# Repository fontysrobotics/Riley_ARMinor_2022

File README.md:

# Riley_ARMinor_2022
Remote indoor Inspection with Low-cost robots (RILey)
## Github file structure
- `docs` : in-development website containing documentation for the RILey robot, as well as pictures of the robot and meta information. Ideally could be run through Github Pages (can be setup in repository settings) but can also be built and run locally through VSCode.
- `documentation` : All documentation created during the project. This includes the initial project information, the plan of approach (before project requirements shifted drastically), datasheets for some of the components, the technical documentation for setting up many aspects of the robot and server systems, plus additional video material.
- `electrical` : Documentation related to the electrical design of the RILey robot, including version 1 and 2 of the PCB design, notes regarding problems encountered in the PCB design and explanations/schematics for the global electrical connections.
- `ros2` : Code files needed to run the robot (physical and simulation) through ROS2-foxy. More info included in technical document. Included are:
  - `riley_ws` : Main ROS workspace containing all the packages and launch files for both robot and server side.
  - `simulation` : ROS workspace used for simulating the robot in a virtual environment (Gazebo).
  - `yolov5` : Separate directory used to store the YOLOv5 object recognition model.
- `solidworks` : Solidworks CAD files making up version 1 and 2 of the RILey robot, including imported assets. Additional folders for STL/DXF component exports also available, though not needed for the CAD assemblies.

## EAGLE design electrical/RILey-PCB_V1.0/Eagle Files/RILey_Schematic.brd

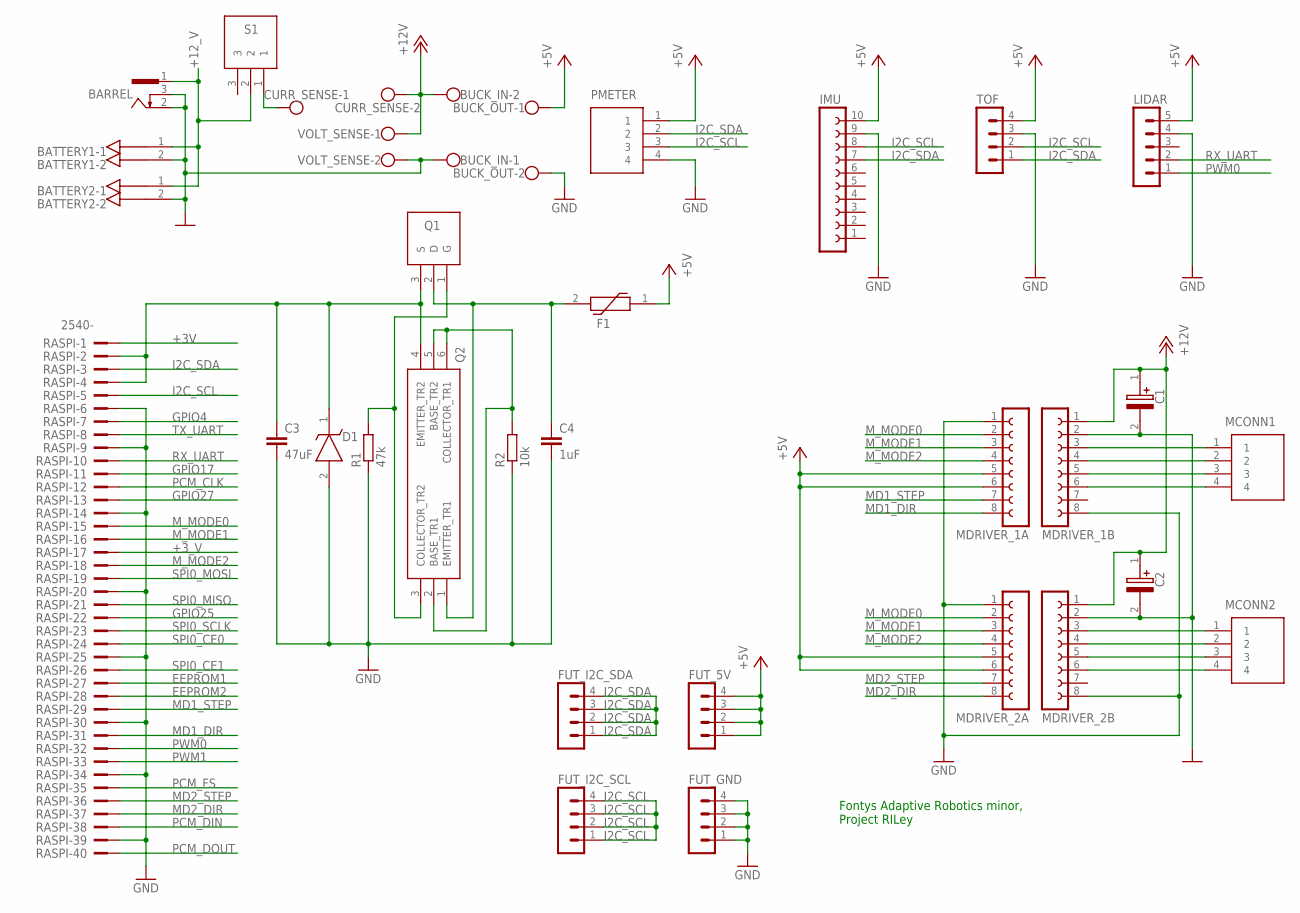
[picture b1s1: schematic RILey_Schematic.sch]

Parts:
BARREL: 733980-62
BATTERY1, BATTERY2: 0026604020; KK41791-4020_2-PIN
BUCK_IN: W237-102
BUCK_OUT: W237-102
C1, C2: 100uF; CAPPRD250W50D655H1250
C3: 47uF; C5B2.5
C4: 1uF; C2.5-3
CURR_SENSE: W237-102
D1: SA5.0A-E3_54; DIOAD1910W86L670D310
F1: PTS18126V260; FUSC4632X90N
FUT_5V: MA04-1
FUT_GND: MA04-1
FUT_I2C_SCL, FUT_I2C_SDA: MA04-1
IMU: FE10-1; FE10
LIDAR: MA05-1
MCONN1, MCONN2: B4B-XH-A_LF__SN_; SHDR4W64P0X250_1X4_1240X575X70
MDRIVER_1A, MDRIVER_1B, MDRIVER_2A, MDRIVER_2B: FE08-1; FE08
PMETER: BLG1X4; RHDR4W64P0X254_1X4_1066X250X86
Q1: IRF9530NPBF; TO254P469X1042X1967-3P
Q2: BCM857BS,115; SOT65P210X110-6N
R1: 47k; 0207/10
R2: 10k; 0207/10
RASPI: 2540-; PAK100/2500-40
S1: 1101M2S3CQE2; 1000-SERIES(SPDT)
TOF: MA04-1
VOLT_SENSE: W237-102

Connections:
0V: BARREL.2, BARREL.3, BATTERY1.2, BATTERY2.2, BUCK_IN.1, C1.2 (-), C2.2 (-), MDRIVER_1B.2, MDRIVER_2B.2, VOLT_SENSE.2
+3V: RASPI.1
+3_V: RASPI.17
+5V: BUCK_OUT.1, F1.1, FUT_5V.1, FUT_5V.2, FUT_5V.3, FUT_5V.4, IMU.10, LIDAR.5, MDRIVER_1A.5, MDRIVER_1A.6, MDRIVER_2A.5, MDRIVER_2A.6, PMETER.1, TOF.4
+12V: BUCK_IN.2, C1.1 (+), C2.1 (+), CURR_SENSE.2, MDRIVER_1B.1, MDRIVER_2B.1, VOLT_SENSE.1
+12_V: BARREL.1, BATTERY1.1, BATTERY2.1, S1.2
EEPROM1: RASPI.27
EEPROM2: RASPI.28
GND: BUCK_OUT.2, C3.2, C4.2, D1.2 (A), FUT_GND.1, FUT_GND.2, FUT_GND.3, FUT_GND.4, IMU.9, LIDAR.4, MDRIVER_1A.1, MDRIVER_1B.8, MDRIVER_2A.1, MDRIVER_2B.8, PMETER.4, R1.1, R2.1, RASPI.6, RASPI.9, RASPI.14, RASPI.20, RASPI.25, RASPI.30, RASPI.34, RASPI.39, TOF.3
GPIO4: RASPI.7
GPIO17: RASPI.11
GPIO25: RASPI.22
GPIO27: RASPI.13
I2C_SCL: FUT_I2C_SCL.1, FUT_I2C_SCL.2, FUT_I2C_SCL.3, FUT_I2C_SCL.4, IMU.8, PMETER.3, RASPI.5, TOF.2
I2C_SDA: FUT_I2C_SDA.1, FUT_I2C_SDA.2, FUT_I2C_SDA.3, FUT_I2C_SDA.4, IMU.7, PMETER.2, RASPI.3, TOF.1
MD1_DIR: MDRIVER_1A.8, RASPI.31
MD1_STEP: MDRIVER_1A.7, RASPI.29
MD2_DIR: MDRIVER_2A.8, RASPI.37
MD2_STEP: MDRIVER_2A.7, RASPI.36
M_MODE0: MDRIVER_1A.2, MDRIVER_2A.2, RASPI.15
M_MODE1: MDRIVER_1A.3, MDRIVER_2A.3, RASPI.16
M_MODE2: MDRIVER_1A.4, MDRIVER_2A.4, RASPI.18
unnamed: MCONN1.1, MDRIVER_1B.3
unnamed: MCONN1.2, MDRIVER_1B.4
unnamed: MCONN1.3, MDRIVER_1B.5
unnamed: MCONN1.4, MDRIVER_1B.6
unnamed: MCONN2.1, MDRIVER_2B.3
unnamed: MCONN2.2, MDRIVER_2B.4
unnamed: MCONN2.3, MDRIVER_2B.5
unnamed: MCONN2.4, MDRIVER_2B.6
unnamed: Q1.1 (G), Q2.3 (COLLECTOR_TR2), R1.2
unnamed: CURR_SENSE.1, S1.1
unnamed: C4.1, F1.2, Q1.2 (D), Q2.1 (EMITTER_TR1)
unnamed: C3.1, D1.1 (K), Q1.3 (S), Q2.4 (EMITTER_TR2), RASPI.2, RASPI.4
unnamed: Q2.2 (BASE_TR1), Q2.5 (BASE_TR2), Q2.6 (COLLECTOR_TR1), R2.2
PCM_CLK: RASPI.12
PCM_DIN: RASPI.38
PCM_DOUT: RASPI.40
PCM_FS: RASPI.35
PWM0: LIDAR.1, RASPI.32
PWM1: RASPI.33
RX_UART: LIDAR.2, RASPI.10
SPI0_CE0: RASPI.24
SPI0_CE1: RASPI.26
SPI0_MISO: RASPI.21
SPI0_MOSI: RASPI.19
SPI0_SCLK: RASPI.23
TX_UART: RASPI.8

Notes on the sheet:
Fontys Adaptive Robotics minor, Project RILey

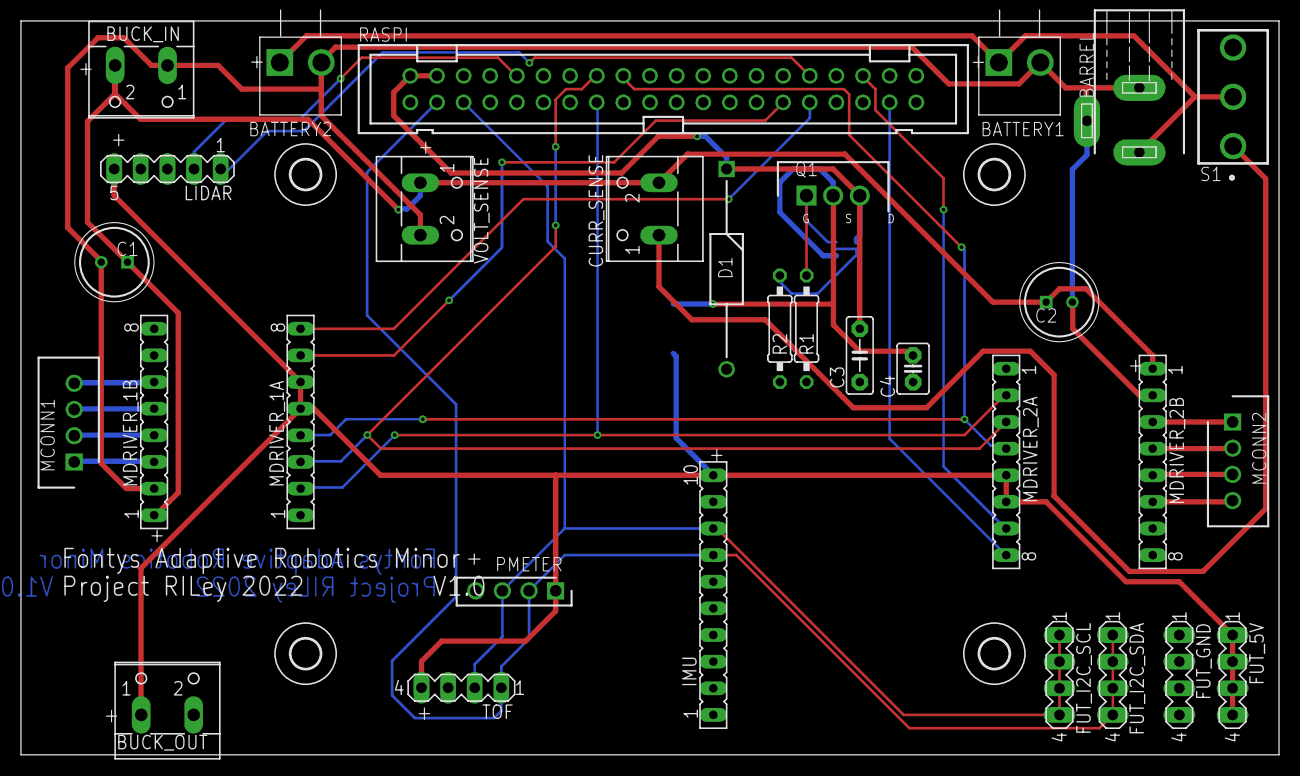
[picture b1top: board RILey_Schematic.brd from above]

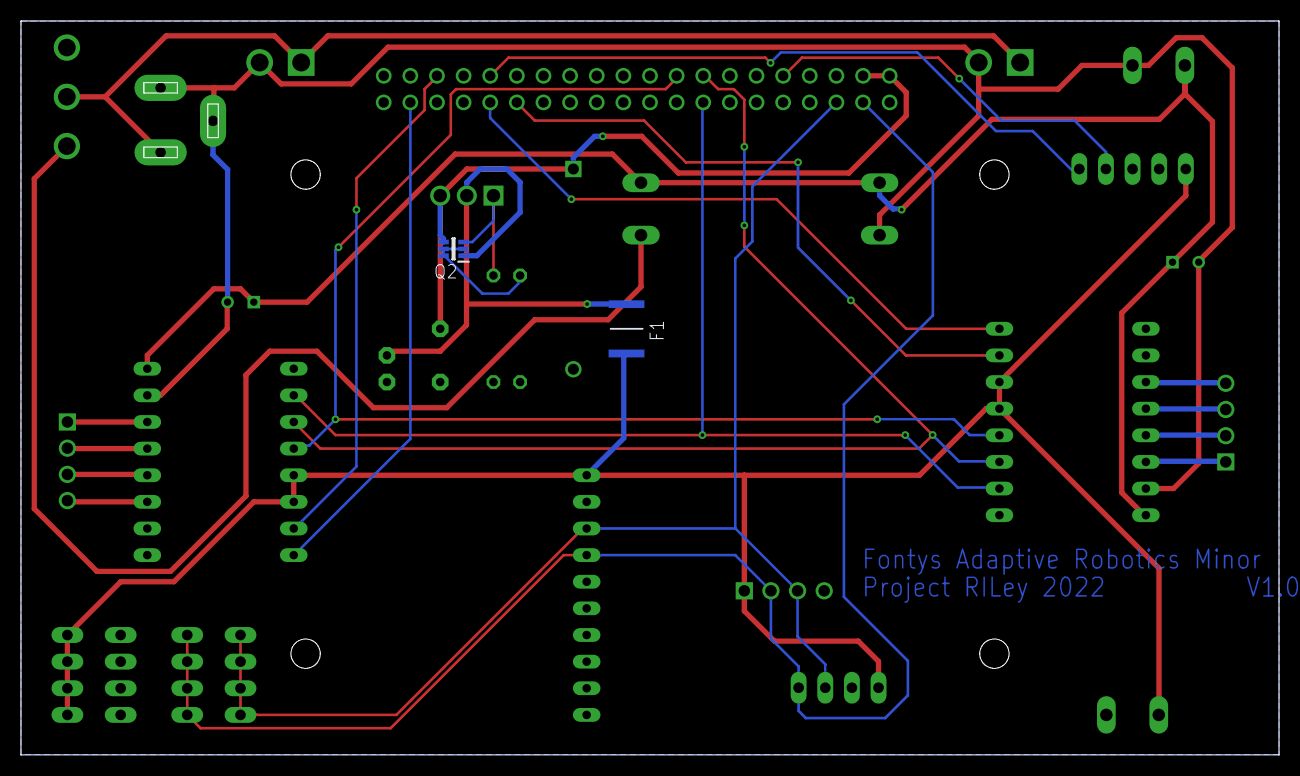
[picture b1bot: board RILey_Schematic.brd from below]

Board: 2 copper layers, 120.0 x 70.0 mm, 37 parts (2 on the bottom side), 29 nets.

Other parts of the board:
U$1, U$3, U$4, U$5: 2,8

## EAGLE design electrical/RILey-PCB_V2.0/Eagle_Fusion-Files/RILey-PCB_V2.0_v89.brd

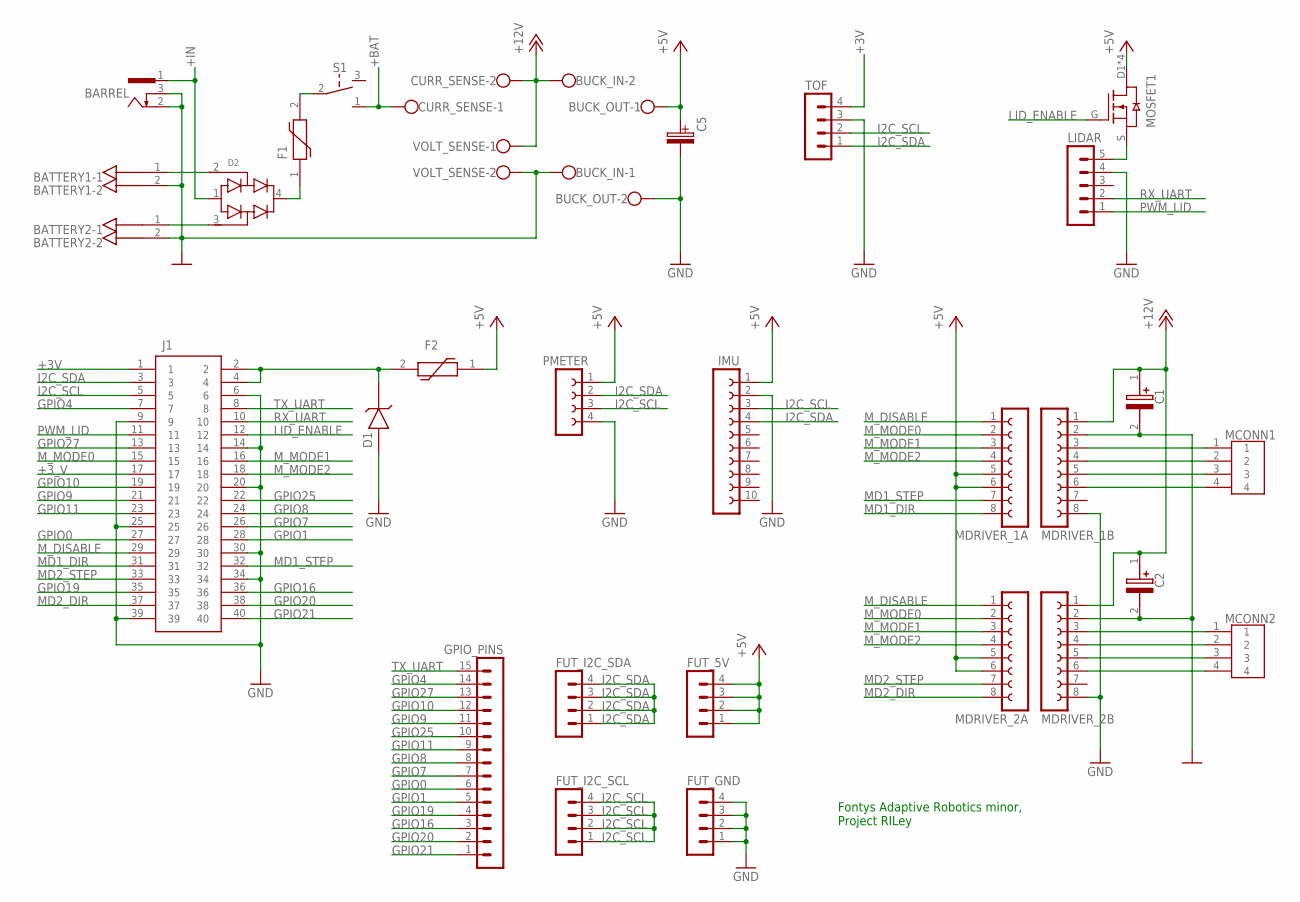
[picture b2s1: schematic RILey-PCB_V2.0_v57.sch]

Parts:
BARREL: DC_BARREL0-62; 733980-62
BATTERY1, BATTERY2: 0026604020; KK41791-4020_2-PIN
BUCK_IN: W237-102
BUCK_OUT: W237-102
C1, C2: 100uF; CAPPRD250W50D655H1250
C5: ELECTROLYTIC_CAPACITOR'8*20'; ELECTROLYTIC_CAPACITOR
CURR_SENSE: W237-102
D1: ZENER-THDO-35; ZENER-TH
D2: DIODE-BRIGDE; DIODE-BRIDGE
F1: 2920L400/15MR
F2: 1812L300MR
FUT_5V: MA04-1_SMALLPAD; MA04-1_S
FUT_GND: MA04-1_SMALLPAD; MA04-1_S
FUT_I2C_SCL, FUT_I2C_SDA: MA04-1_SMALLPAD; MA04-1_S
GPIO_PINS: MA15-1W
IMU: FE10-1_3D; FE10-1
J1: MC-254-40-00-ST-DIP
LIDAR: MA05-1_SMALLPAD; MA05-1_S
MCONN1, MCONN2: B4B-XH-A_LF__SN_
MDRIVER_1A, MDRIVER_1B, MDRIVER_2A, MDRIVER_2B: FE08-1_3D; FE08-1
MOSFET1: SI2303CDS-T1-GE3; TSOP6_SOT457
PMETER: FE04-1
S1: 1101M2S3CQE2; 1000-SERIES(SPDT)
TOF: MA04-1W
VOLT_SENSE: W237-102

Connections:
0V: BARREL.2, BARREL.3, BATTERY1.2, BATTERY2.2, BUCK_IN.1, C1.2 (-), C2.2 (-), MDRIVER_1B.2, MDRIVER_2B.2, VOLT_SENSE.2
+3V: J1.1, TOF.4
+3_V: J1.17
+5V: BUCK_OUT.1, C5.+, F2.1, FUT_5V.1, FUT_5V.2, FUT_5V.3, FUT_5V.4, IMU.1, MDRIVER_1A.5, MDRIVER_1A.6, MDRIVER_2A.5, MDRIVER_2A.6, MOSFET1.D1 (D), MOSFET1.D2 (D), MOSFET1.D3 (D), MOSFET1.D4 (D), PMETER.1
+5V_FUSED: D1.C, F2.2, J1.2, J1.4
+12V: BUCK_IN.2, C1.1 (+), C2.1 (+), CURR_SENSE.2, MDRIVER_1B.1, MDRIVER_2B.1, VOLT_SENSE.1
+BAT: CURR_SENSE.1, S1.1
+BAT1: BATTERY1.1, D2.2
+BAT2: BATTERY2.1, D2.3
+IN: BARREL.1, D2.1
GND: BUCK_OUT.2, C5.-, D1.A, FUT_GND.1, FUT_GND.2, FUT_GND.3, FUT_GND.4, IMU.2, J1.6, J1.9, J1.14, J1.20, J1.25, J1.30, J1.34, J1.39, LIDAR.4, MDRIVER_1B.8, MDRIVER_2B.8, PMETER.4, TOF.3
GPIO0: GPIO_PINS.6, J1.27
GPIO1: GPIO_PINS.5, J1.28
GPIO4: GPIO_PINS.14, J1.7
GPIO7: GPIO_PINS.7, J1.26
GPIO8: GPIO_PINS.8, J1.24
GPIO9: GPIO_PINS.11, J1.21
GPIO10: GPIO_PINS.12, J1.19
GPIO11: GPIO_PINS.9, J1.23
GPIO16: GPIO_PINS.3, J1.36
GPIO19: GPIO_PINS.4, J1.35
GPIO20: GPIO_PINS.2, J1.38
GPIO21: GPIO_PINS.1, J1.40
GPIO25: GPIO_PINS.10, J1.22
GPIO27: GPIO_PINS.13, J1.13
I2C_SCL: FUT_I2C_SCL.1, FUT_I2C_SCL.2, FUT_I2C_SCL.3, FUT_I2C_SCL.4, IMU.3, J1.5, PMETER.3, TOF.2
I2C_SDA: FUT_I2C_SDA.1, FUT_I2C_SDA.2, FUT_I2C_SDA.3, FUT_I2C_SDA.4, IMU.4, J1.3, PMETER.2, TOF.1
IN: D2.4, F1.1
LID_ENABLE: J1.12, MOSFET1.G
MD1_DIR: J1.31, MDRIVER_1A.8
MD1_STEP: J1.32, MDRIVER_1A.7
MD2_DIR: J1.37, MDRIVER_2A.8
MD2_STEP: J1.33, MDRIVER_2A.7
M_DISABLE: J1.29, MDRIVER_1A.1, MDRIVER_2A.1
M_MODE0: J1.15, MDRIVER_1A.2, MDRIVER_2A.2
M_MODE1: J1.16, MDRIVER_1A.3, MDRIVER_2A.3
M_MODE2: J1.18, MDRIVER_1A.4, MDRIVER_2A.4
unnamed: LIDAR.5, MOSFET1.S
unnamed: F1.2, S1.2
unnamed: MCONN1.1, MDRIVER_1B.3
unnamed: MCONN1.2, MDRIVER_1B.4
unnamed: MCONN1.3, MDRIVER_1B.5
unnamed: MCONN1.4, MDRIVER_1B.6
unnamed: MCONN2.1, MDRIVER_2B.3
unnamed: MCONN2.2, MDRIVER_2B.4
unnamed: MCONN2.3, MDRIVER_2B.5
unnamed: MCONN2.4, MDRIVER_2B.6
PWM_LID: J1.11, LIDAR.1
RX_UART: J1.10, LIDAR.2
TX_UART: GPIO_PINS.15, J1.8

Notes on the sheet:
Fontys Adaptive Robotics minor, Project RILey

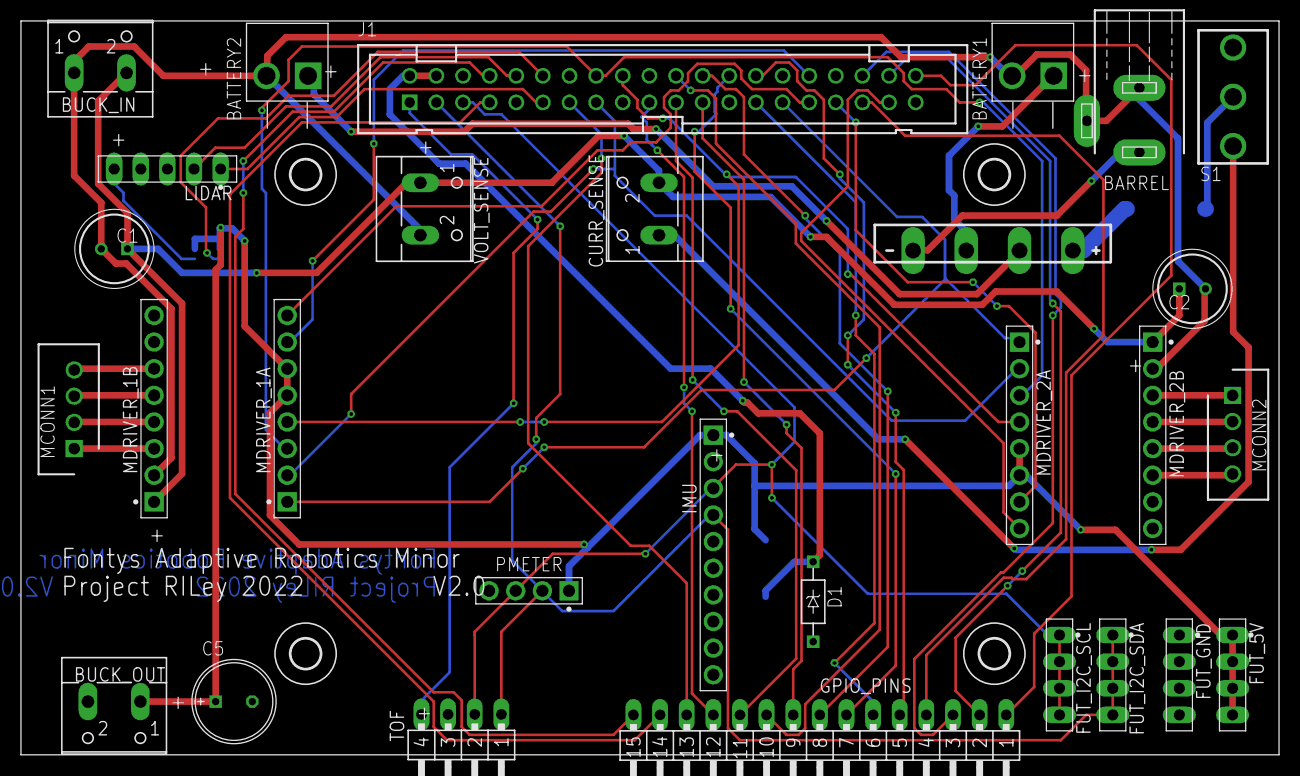
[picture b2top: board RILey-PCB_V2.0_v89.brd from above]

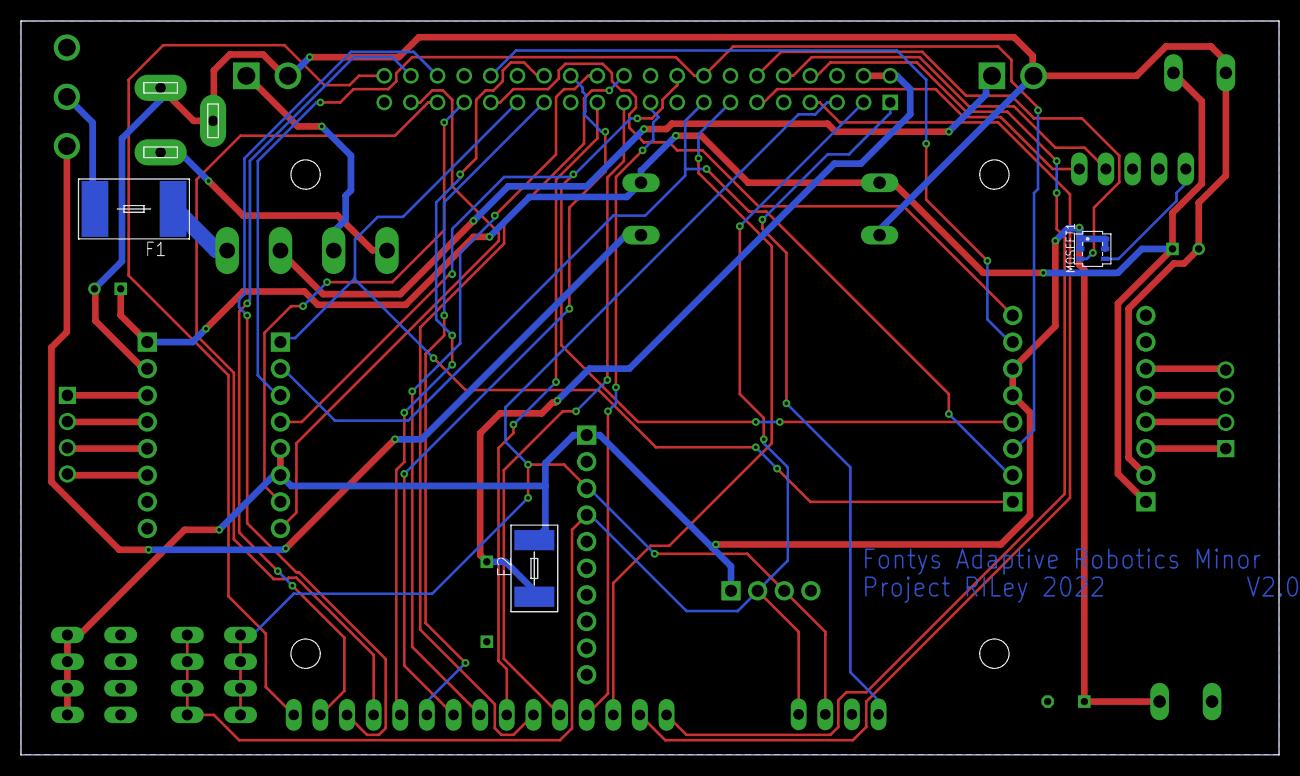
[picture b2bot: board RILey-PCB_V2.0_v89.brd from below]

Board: 2 copper layers, 120.0 x 70.0 mm, 36 parts (3 on the bottom side), 49 nets.

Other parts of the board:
U$1, U$3, U$4, U$5: 2,8

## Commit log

2022-07-08 Initial migrating of RILey git repo to fontys repo
2022-07-11 Synced website changes

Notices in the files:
parts and their libraries:
molex: Creative Commons Attribution-ShareAlike 3.0 Unported (CC BY-SA 3.0), http://creativecommons.org/licenses/by-sa/3.0/.
